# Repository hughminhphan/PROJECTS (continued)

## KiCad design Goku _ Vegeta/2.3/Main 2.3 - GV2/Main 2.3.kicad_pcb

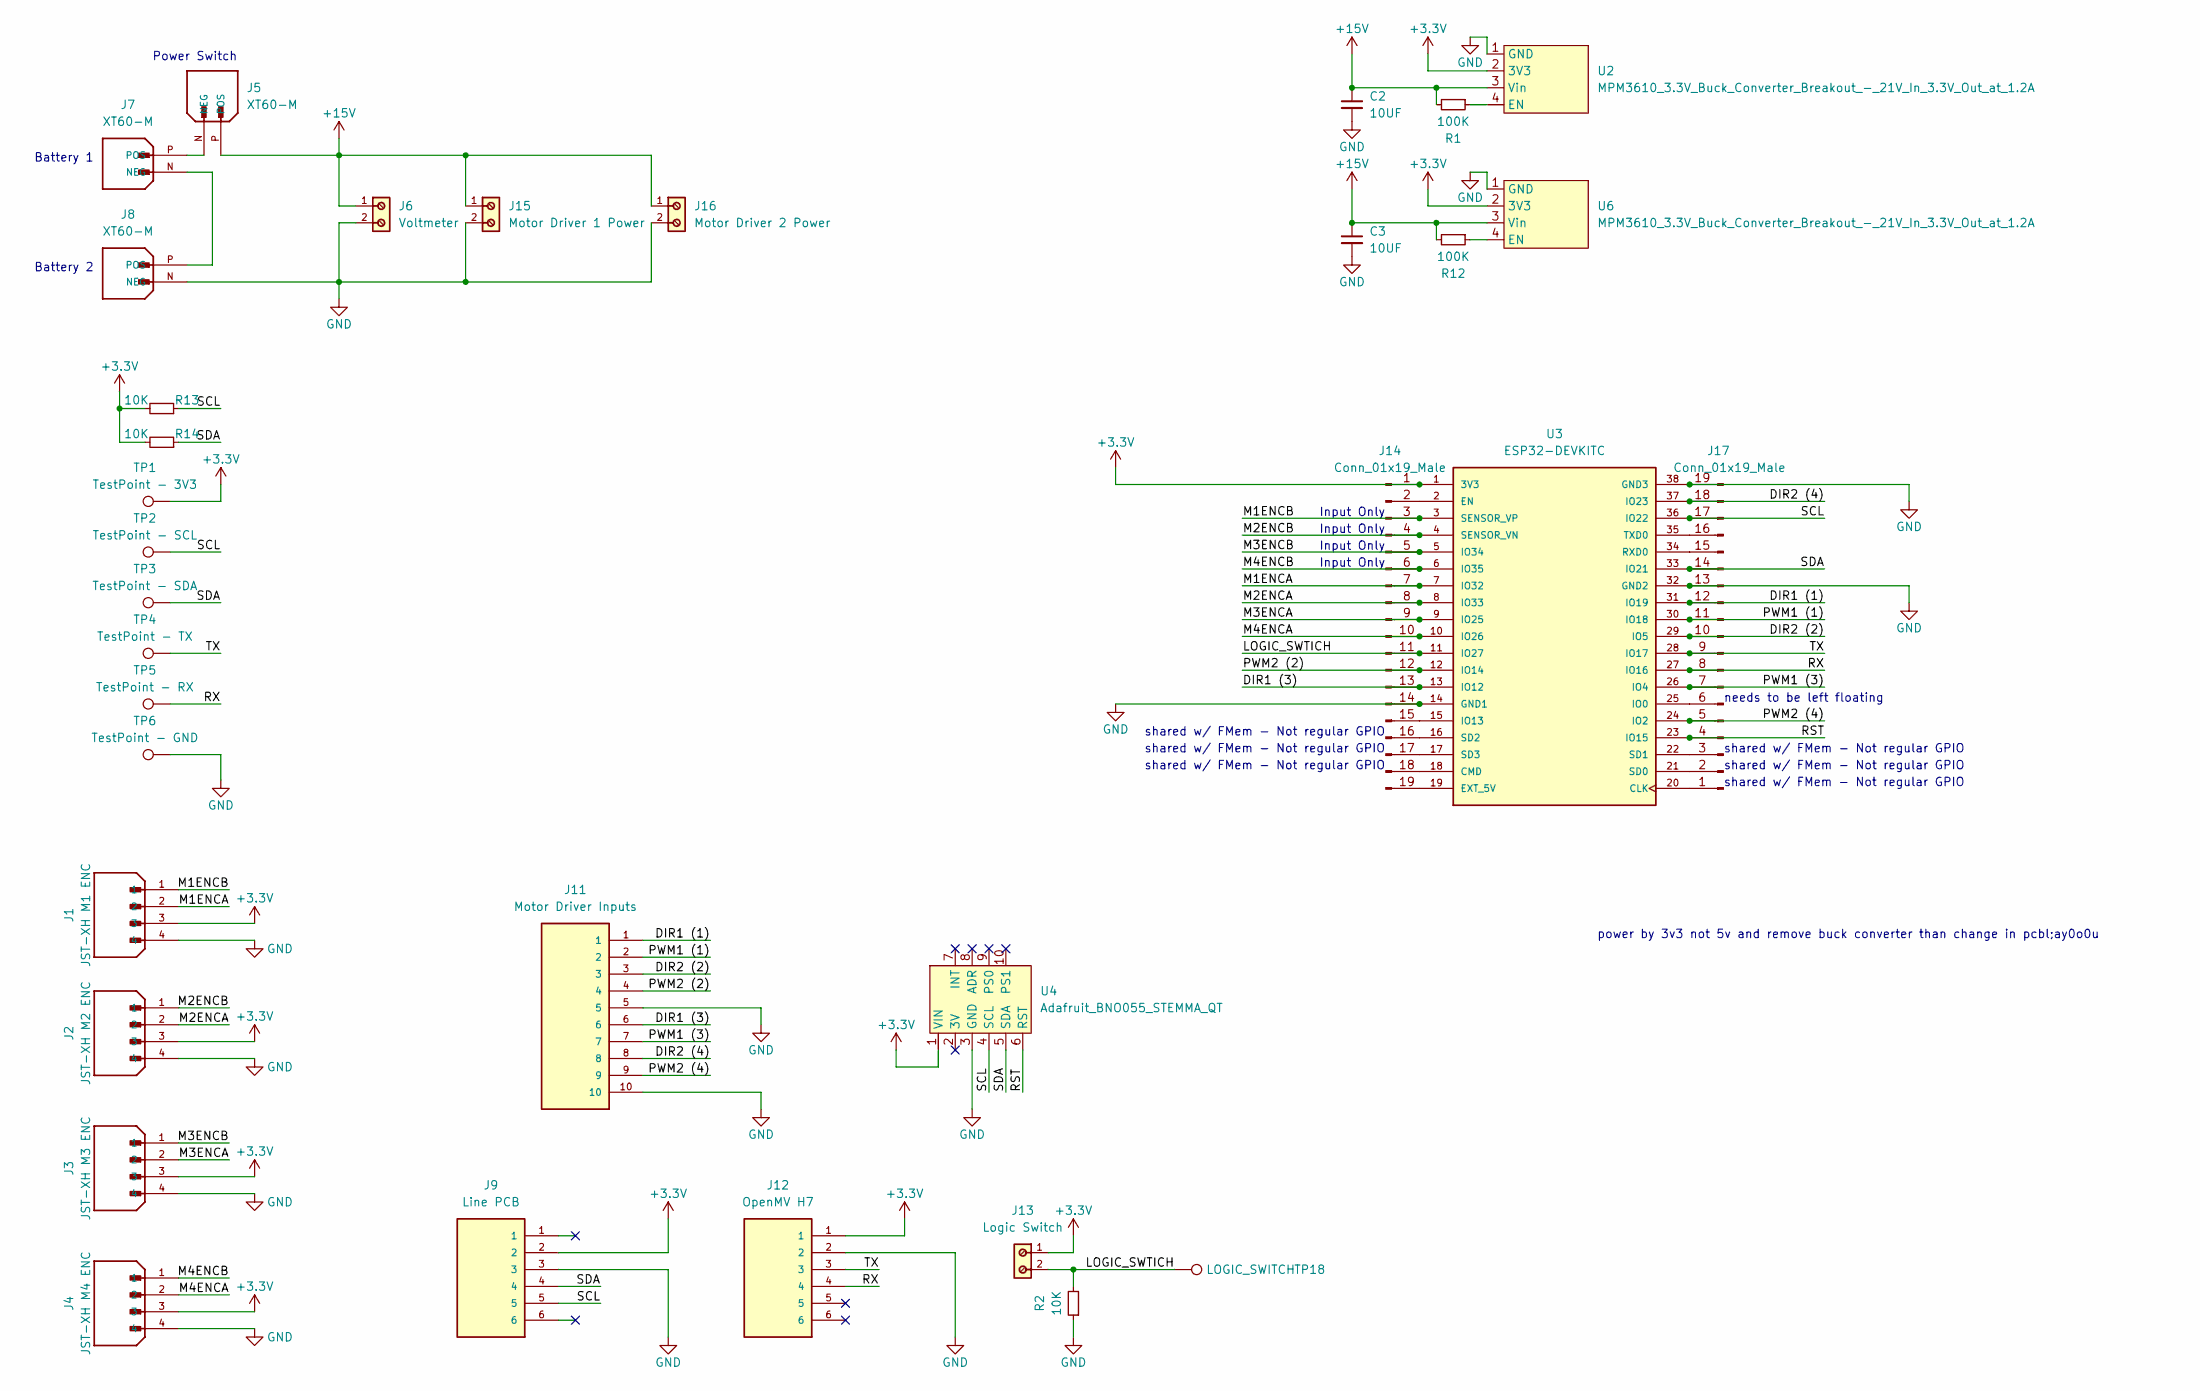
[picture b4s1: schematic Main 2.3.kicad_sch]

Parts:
C2, C3: 10UF; C_0805_2012Metric
J1: JST-XH M1 ENC; JST_B4B-XH-A(LF)(SN); PARTREV N/A
J2: JST-XH M2 ENC; JST_B4B-XH-A(LF)(SN); PARTREV N/A
J3: JST-XH M3 ENC; JST_B4B-XH-A(LF)(SN); PARTREV N/A
J4: JST-XH M4 ENC; JST_B4B-XH-A(LF)(SN); PARTREV N/A
J5, J7, J8: XT60-M; PARTREV V1.2
J6: Voltmeter; 5mm Pitch 2-Pin Screw Terminal Block; PART-NUMBER 691137710002
J9: Line PCB; Box IDC header 2x3
J11: Motor Driver Inputs; Box IDC header 2x5
J12: OpenMV H7; Box IDC header 2x3
J13: Logic Switch; 5mm Pitch 2-Pin Screw Terminal Block; PART-NUMBER 691137710002
J14, J17: Conn_01x19_Male; PinHeader_1x19_P2.54mm_Vertical
J15: Motor Driver 1 Power; 5mm Pitch 2-Pin Screw Terminal Block; PART-NUMBER 691137710002
J16: Motor Driver 2 Power; 5mm Pitch 2-Pin Screw Terminal Block; PART-NUMBER 691137710002
R1, R12: 100K; R_0805_2012Metric
R2, R13, R14: 10K; R_0805_2012Metric
TP1: TestPoint - 3V3; TestPoint_THTPad_D2.0mm_Drill1.0mm
TP2: TestPoint - SCL; TestPoint_THTPad_D2.0mm_Drill1.0mm
TP3: TestPoint - SDA; TestPoint_THTPad_D2.0mm_Drill1.0mm
TP4: TestPoint - TX; TestPoint_THTPad_D2.0mm_Drill1.0mm
TP5: TestPoint - RX; TestPoint_THTPad_D2.0mm_Drill1.0mm
TP6: TestPoint - GND; TestPoint_THTPad_D2.0mm_Drill1.0mm
TP18: LOGIC_SWITCH; TestPoint_THTPad_D2.0mm_Drill1.0mm
U2, U6: MPM3610_3.3V_Buck_Converter_Breakout_-_21V_In_3.3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; MPM3610 3.3V Buck Converter Breakout - 21V In 3.3V Out at 1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
U3: ESP32-DEVKITC; MODULE_ESP32-DEVKITC; PARTREV N/A
U4: Adafruit_BNO055_STEMMA_QT; Adafruit IMU BNO055

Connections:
+3.3V: J1.3, J2.3, J3.3, J4.3, J9.2, J12.1, J13.1, J14.1, R13.2, R14.2, TP1.1, U2.2 (3V3), U3.1 (3V3), U4.1 (VIN), U6.2 (3V3)
+15V: C2.1, C3.1, J5.P (POS), J6.1, J15.1, J16.1, R1.2, R12.2, U2.3 (Vin), U6.3 (Vin)
/DIR1 (1): J11.1, J17.12, U3.31 (IO19)
/DIR1 (3): J11.6, J14.13, U3.13 (IO12)
/DIR2 (2): J11.3, J17.10, U3.29 (IO5)
/DIR2 (4): J11.8, J17.18, U3.37 (IO23)
/LOGIC_SWTICH: J13.2, J14.11, R2.2, TP18.1, U3.11 (IO27)
/M1ENCA: J1.2, J14.7, U3.7 (IO32)
/M1ENCB: J1.1, J14.3, U3.3 (SENSOR_VP)
/M2ENCA: J2.2, J14.8, U3.8 (IO33)
/M2ENCB: J2.1, J14.4, U3.4 (SENSOR_VN)
/M3ENCA: J3.2, J14.9, U3.9 (IO25)
/M3ENCB: J3.1, J14.5, U3.5 (IO34)
/M4ENCA: J4.2, J14.10, U3.10 (IO26)
/M4ENCB: J4.1, J14.6, U3.6 (IO35)
/PWM1 (1): J11.2, J17.11, U3.30 (IO18)
/PWM1 (3): J11.7, J17.7, U3.26 (IO4)
/PWM2 (2): J11.4, J14.12, U3.12 (IO14)
/PWM2 (4): J11.9, J17.5, U3.24 (IO2)
/RST: J17.4, U3.23 (IO15), U4.6 (RST)
/RX: J12.4, J17.8, TP5.1, U3.27 (IO16)
/SCL: J9.5, J17.17, R13.1, TP2.1, U3.36 (IO22), U4.4 (SCL)
/SDA: J9.4, J17.14, R14.1, TP3.1, U3.33 (IO21), U4.5 (SDA)
/TX: J12.3, J17.9, TP4.1, U3.28 (IO17)
GND: C2.2, C3.2, J1.4, J2.4, J3.4, J4.4, J6.2, J8.N (NEG), J9.3, J11.5, J11.10, J12.2, J14.14, J15.2, J16.2, J17.13, J17.19, R2.1, TP6.1, U2.1 (GND), U3.14 (GND1), U3.32 (GND2), U3.38 (GND3), U4.3 (GND), U6.1 (GND)
unnamed: J5.N (NEG), J7.P (POS)
unnamed: J7.N (NEG), J8.P (POS)
unnamed: J14.2, U3.2 (EN)
unnamed: J14.15, U3.15 (IO13)
unnamed: J14.16, U3.16 (SD2)
unnamed: J14.17, U3.17 (SD3)
unnamed: J14.18, U3.18 (CMD)
unnamed: J14.19, U3.19 (EXT_5V)
unnamed: J17.1, U3.20 (CLK)
unnamed: J17.2, U3.21 (SD0)
unnamed: J17.3, U3.22 (SD1)
unnamed: J17.6, U3.25 (IO0)
unnamed: J17.15, U3.34 (RXD0)
unnamed: J17.16, U3.35 (TXD0)
unnamed: R1.1, U2.4 (EN)
unnamed: R12.1, U6.4 (EN)

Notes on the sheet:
Input Only
shared w/ FMem - Not regular GPIO
needs to be left floating
Battery 1
Power Switch
power by 3v3 not 5v and remove buck converter than change in pcbl;ay0o0u
Battery 2

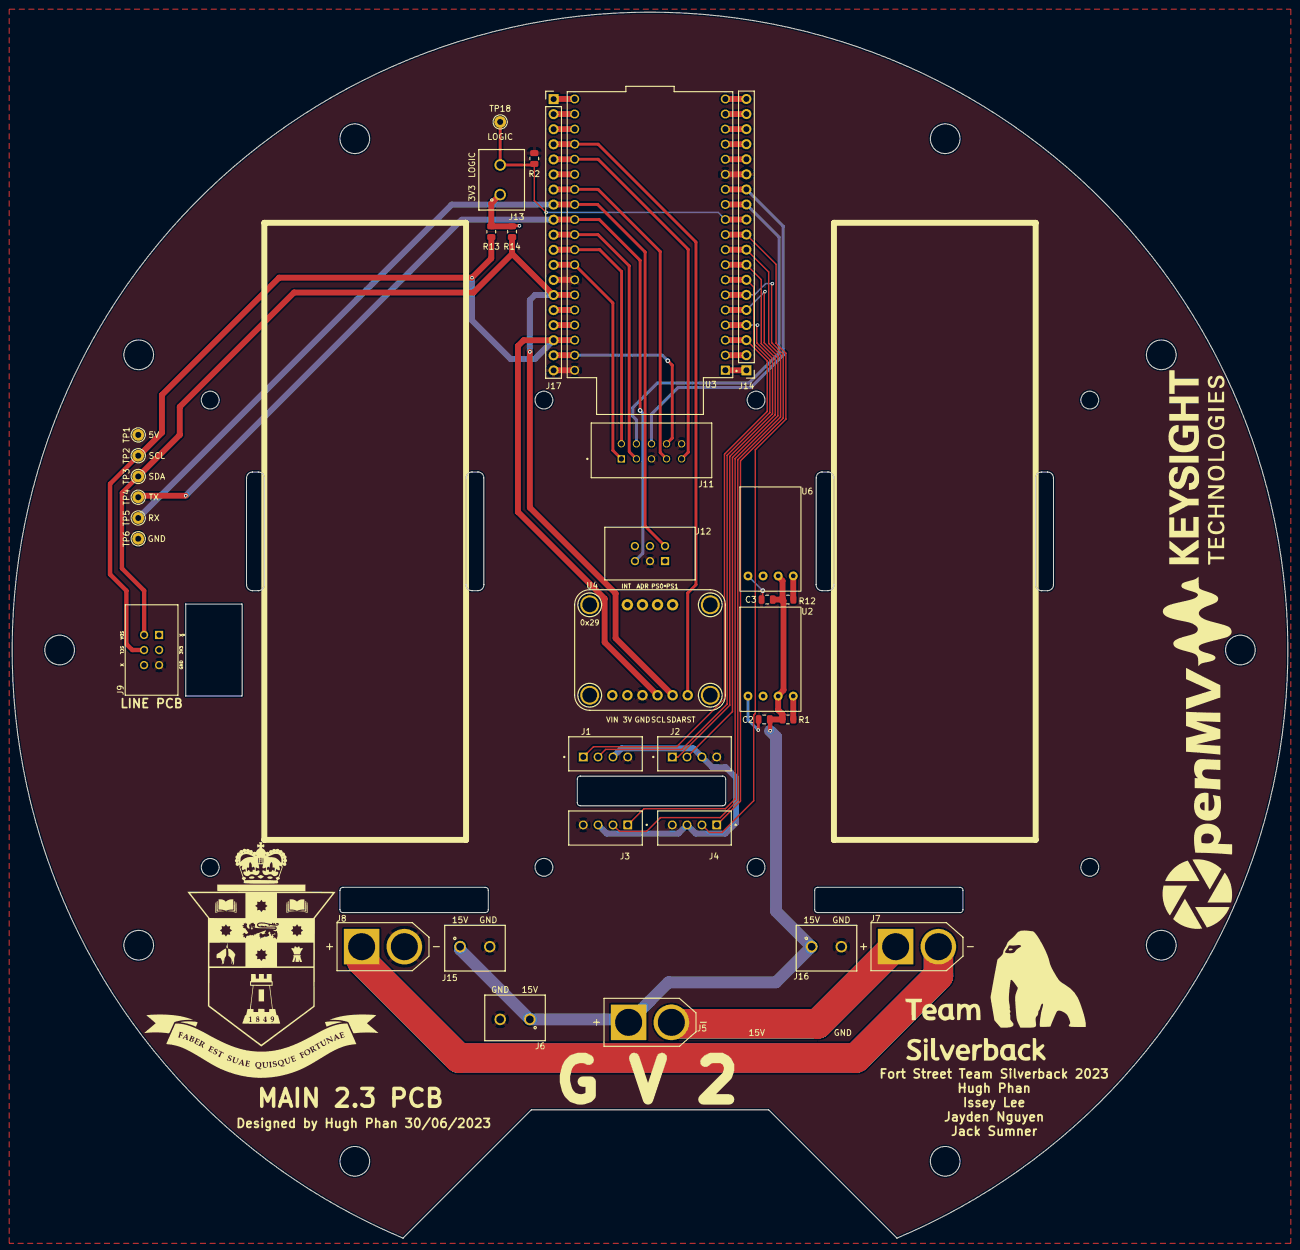
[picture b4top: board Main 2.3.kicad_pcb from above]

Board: 2 copper layers, 215.0 x 206.6 mm, 34 parts (0 on the bottom side), 41 nets.

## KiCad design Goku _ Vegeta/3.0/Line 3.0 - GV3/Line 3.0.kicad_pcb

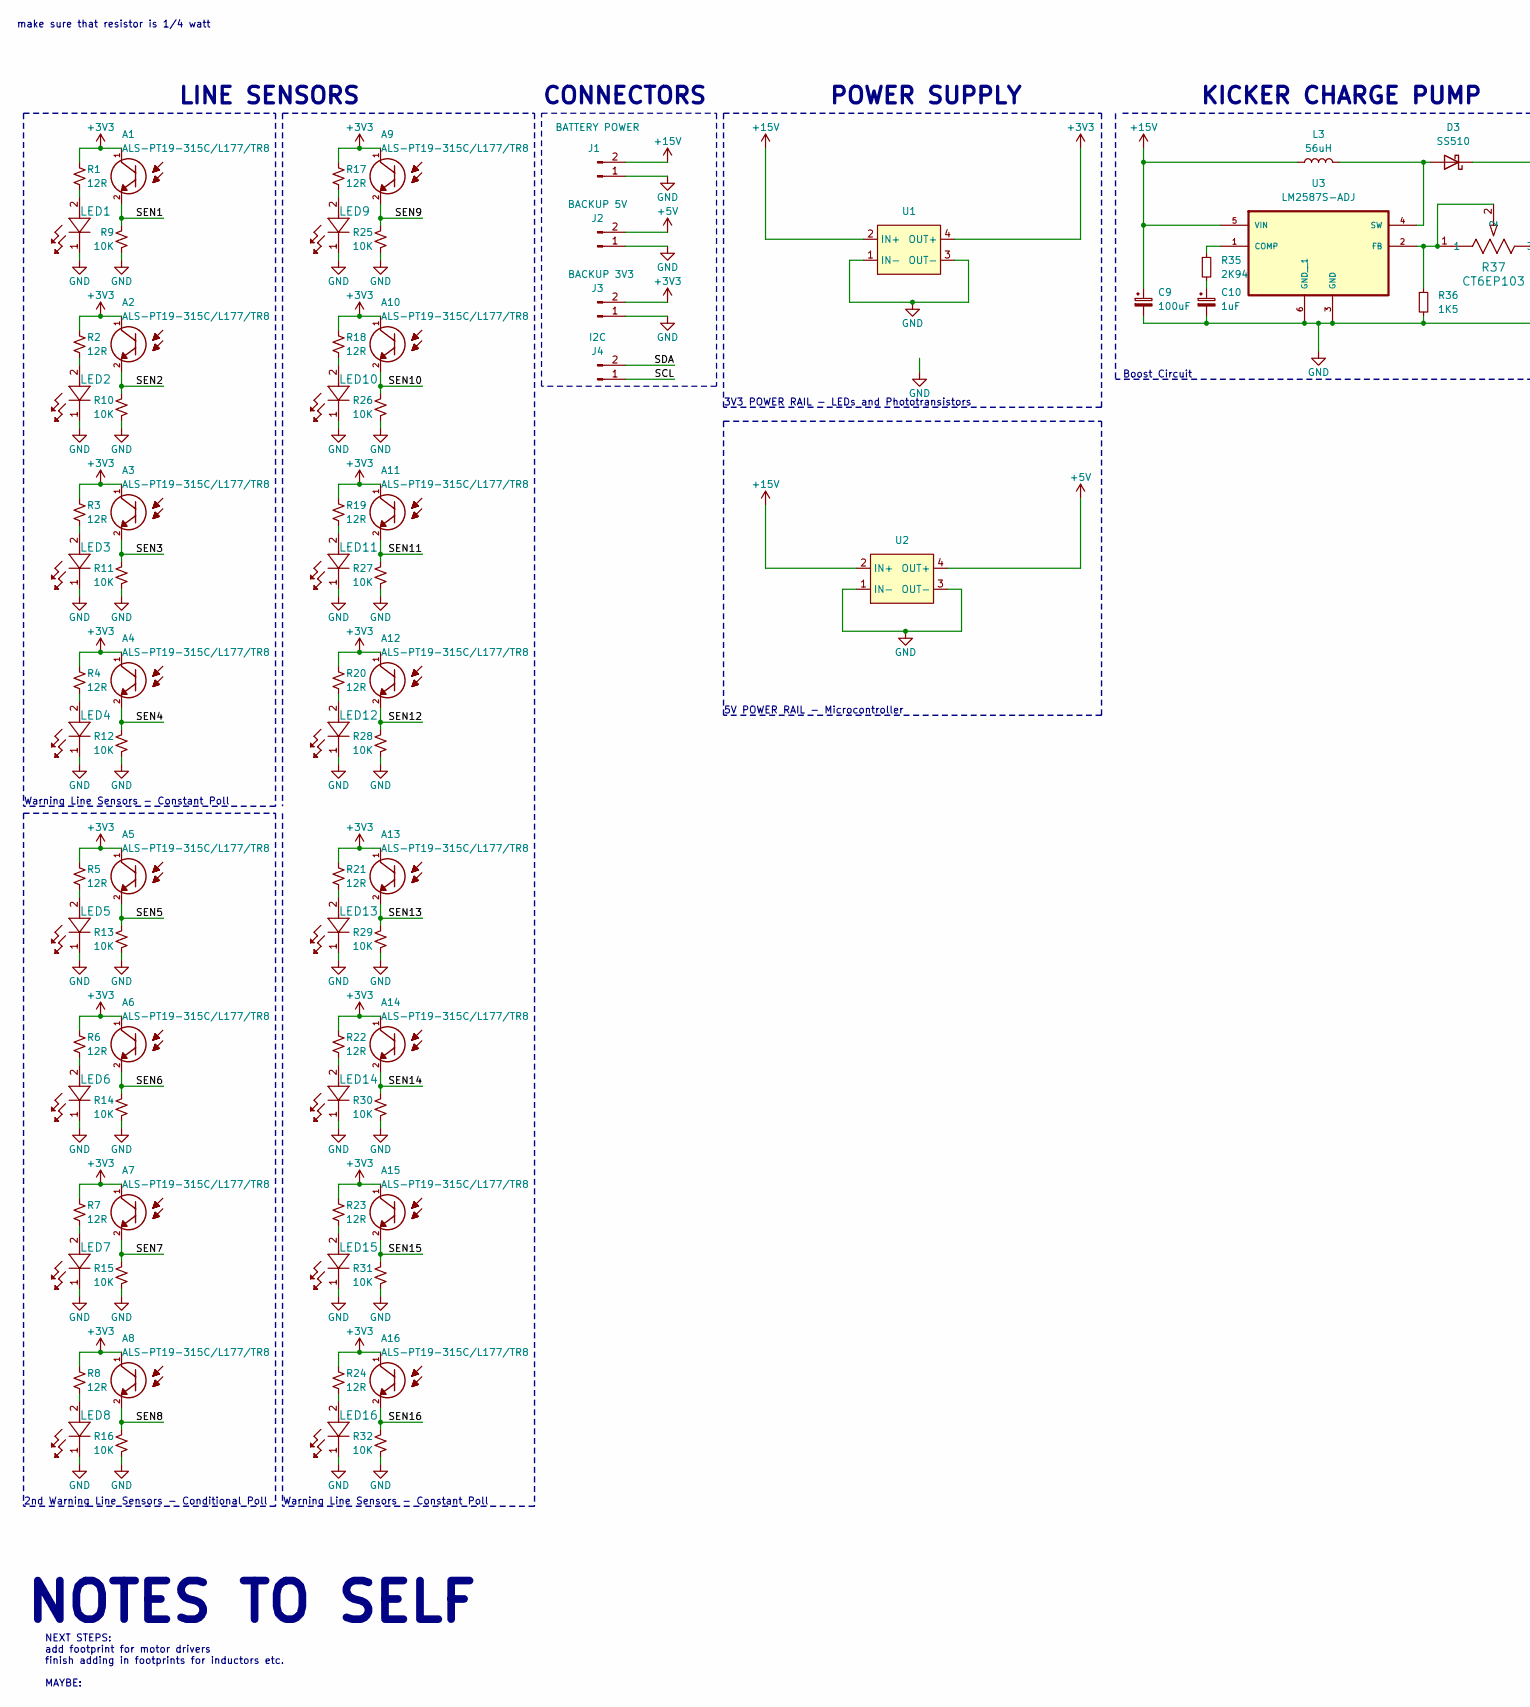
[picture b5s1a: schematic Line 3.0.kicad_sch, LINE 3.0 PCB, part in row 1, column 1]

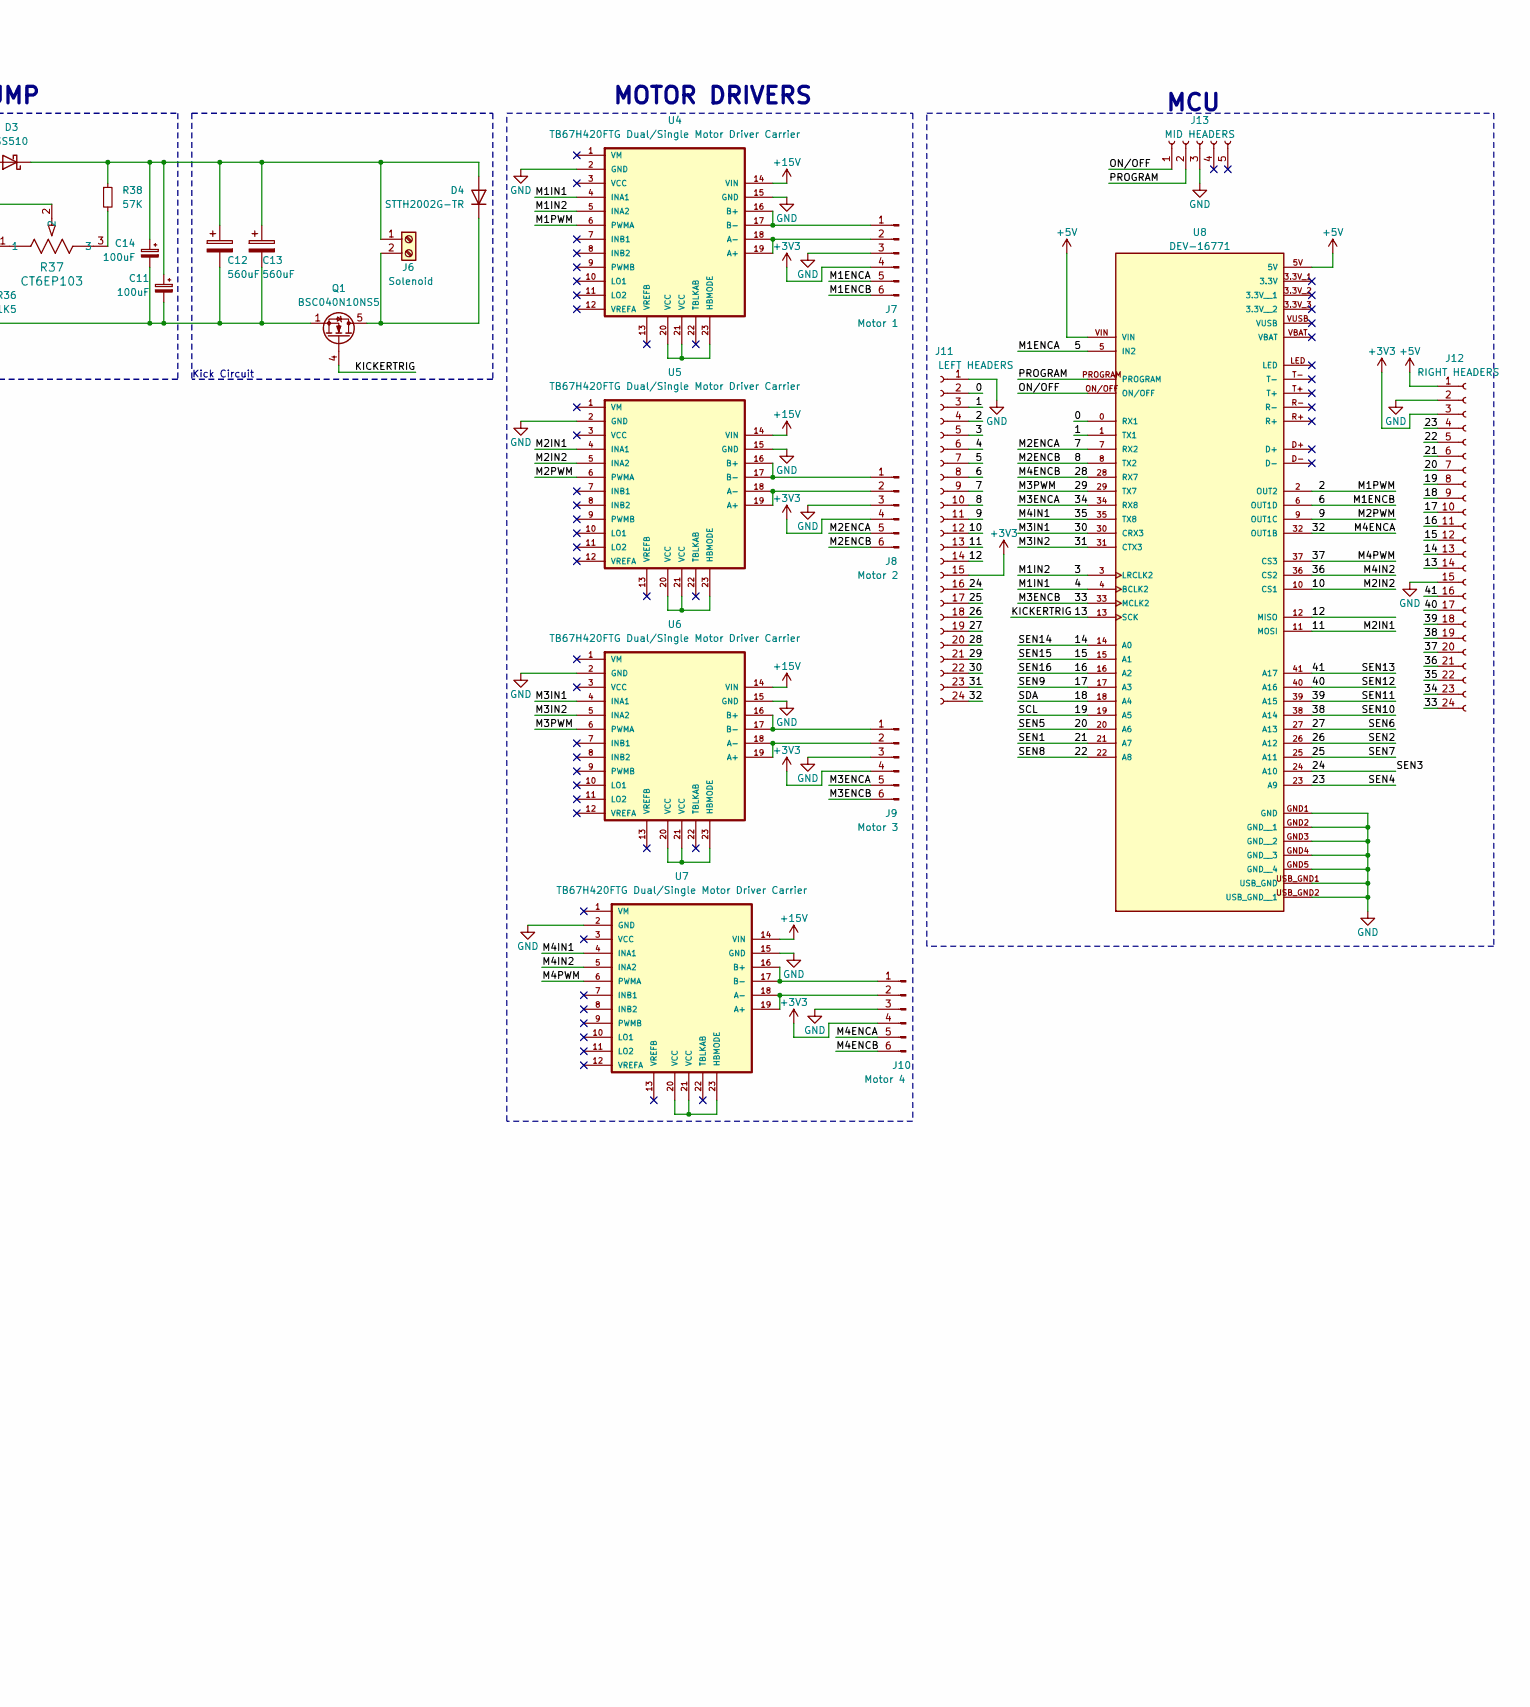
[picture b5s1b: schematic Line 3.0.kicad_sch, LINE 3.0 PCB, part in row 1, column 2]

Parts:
A1, A2, A3, A4, A5, A6, A7, A8, A9, A10, A11, A12, A13, A14, A15, A16: ALS-PT19-315C/L177/TR8; XDCR_ALS-PT19-315C_L177_TR8; PARTREV 5
C9, C11, C14: 100uF; CP_Radial_D10.0mm_P5.00mm
C10: 1uF; C_0805_2012Metric
C12, C13: 560uF; CP_Radial_D18.0mm_P7.50mm
D3: SS510; D_SMC
D4: STTH2002G-TR; TO-263-2
J1: BATTERY POWER; AMASS_XT60-F_1x02_P7.20mm_Vertical
J2: BACKUP 5V; AMASS_XT30U-F_1x02_P5.0mm_Vertical
J3: BACKUP 3V3; AMASS_XT30U-F_1x02_P5.0mm_Vertical
J4: I2C; AMASS_XT30U-F_1x02_P5.0mm_Vertical
J6: Solenoid; TerminalBlock_bornier-2_P5.08mm
J7: Motor 1; PinSocket_1x06_P2.54mm_Vertical
J8: Motor 2; PinSocket_1x06_P2.54mm_Vertical
J9: Motor 3; PinSocket_1x06_P2.54mm_Vertical
J10: Motor 4; PinSocket_1x06_P2.54mm_Vertical
J11: LEFT HEADERS; PinHeader_1x24_P2.54mm_Vertical
J12: RIGHT HEADERS; PinHeader_1x24_P2.54mm_Vertical
J13: MID HEADERS; PinHeader_1x05_P2.54mm_Vertical
L3: 56uH; L_Bourns_SRR1260
LED1, LED2, LED3, LED4, LED5, LED6, LED7, LED8, LED9, LED10, LED11, LED12, LED13, LED14, LED15, LED16: JB2835AWT-W-U30GA0000-N0000001; LED_J2835_CRW
Q1: BSC040N10NS5; TDSON-8-1
R1, R2, R3, R4, R5, R6, R7, R8, R17, R18, R19, R20, R21, R22, R23, R24: 12R; R_0805_2012Metric
R9, R10, R11, R12, R13, R14, R15, R16, R25, R26, R27, R28, R29, R30, R31, R32: 10K; R_0805_2012Metric
R35: 2K94; R_0805_2012Metric
R36: 1K5; R_0805_2012Metric
R37: CT6EP103; POT_CT-6EP_NDC
R38: 57K; R_0805_2012Metric
U1, U2: DC-DC Multi-output Buck Converter
U3: LM2587S-ADJ; VREG_TPS79625KTTR
U4, U5, U6, U7: TB67H420FTG Dual/Single Motor Driver Carrier; TB67H420FTG DualSingle Motor Driver Carrier
U8: DEV-16771; MODULE_DEV-16771; PARTREV 4.1

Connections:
+3V3: A1.1, A2.1, A3.1, A4.1, A5.1, A6.1, A7.1, A8.1, A9.1, A10.1, A11.1, A12.1, A13.1, A14.1, A15.1, A16.1, J3.2, J7.4, J8.4, J9.4, J10.4, J11.15, J12.3, R1.1, R2.1, R3.1, R4.1, R5.1, R6.1, R7.1, R8.1, R17.1, R18.1, R19.1, R20.1, R21.1, R22.1, R23.1, R24.1, U1.4 (OUT+); also elsewhere on the board
+5V: J2.2, J12.1, U2.4 (OUT+), U8.5V, U8.VIN; also elsewhere on the board
+15V: C9.1, J1.2, L3.1, U1.2 (IN+), U2.2 (IN+), U3.5 (VIN), U4.14 (VIN), U5.14 (VIN), U6.14 (VIN), U7.14 (VIN)
/0: J11.2, U8.0 (RX1)
/1: J11.3, U8.1 (TX1)
/2: J11.4, U4.6 (PWMA), U8.2 (OUT2)
/3: J11.5, U4.5 (INA2), U8.3 (LRCLK2)
/4: J11.6, U4.4 (INA1), U8.4 (BCLK2)
/5: J7.5, J11.7, U8.5 (IN2)
/6: J7.6, J11.8, U8.6 (OUT1D)
/7: J8.5, J11.9, U8.7 (RX2)
/8: J8.6, J11.10, U8.8 (TX2)
/9: J11.11, U5.6 (PWMA), U8.9 (OUT1C)
/10: J11.12, U5.5 (INA2), U8.10 (CS1)
/11: J11.13, U5.4 (INA1), U8.11 (MOSI)
/12: J11.14, U8.12 (MISO)
/13: J12.14, Q1.4 (G), U8.13 (SCK)
/14: A14.2, J12.13, R30.2, U8.14 (A0)
/15: A15.2, J12.12, R31.2, U8.15 (A1)
/16: A16.2, J12.11, R32.2, U8.16 (A2)
/17: A9.2, J12.10, R25.2, U8.17 (A3)
/18: J4.2, J12.9, U8.18 (A4)
/19: J4.1, J12.8, U8.19 (A5)
/20: A5.2, J12.7, R13.2, U8.20 (A6)
/21: A1.2, J12.6, R9.2, U8.21 (A7)
/22: A8.2, J12.5, R16.2, U8.22 (A8)
/23: A4.2, J12.4, R12.2, U8.23 (A9)
/24: A3.2, J11.16, R11.2, U8.24 (A10)
/25: A7.2, J11.17, R15.2, U8.25 (A11)
/26: A2.2, J11.18, R10.2, U8.26 (A12)
/27: A6.2, J11.19, R14.2, U8.27 (A13)
/28: J10.6, J11.20, U8.28 (RX7)
/29: J11.21, U6.6 (PWMA), U8.29 (TX7)
/30: J11.22, U6.4 (INA1), U8.30 (CRX3)
/31: J11.23, U6.5 (INA2), U8.31 (CTX3)
/32: J10.5, J11.24, U8.32 (OUT1B)
/33: J9.6, J12.24, U8.33 (MCLK2)
/34: J9.5, J12.23, U8.34 (RX8)
/35: J12.22, U7.4 (INA1), U8.35 (TX8)
/36: J12.21, U7.5 (INA2), U8.36 (CS2)
/37: J12.20, U7.6 (PWMA), U8.37 (CS3)
/38: A10.2, J12.19, R26.2, U8.38 (A14)
/39: A11.2, J12.18, R27.2, U8.39 (A15)
/40: A12.2, J12.17, R28.2, U8.40 (A16)
/41: A13.2, J12.16, R29.2, U8.41 (A17)
/ON/OFF: J13.1, U8.ON/OFF
/PROGRAM: J13.2, U8.PROGRAM
GND: C9.2, C10.2, C11.2, C12.2, C13.2, C14.2, J1.1, J2.1, J3.1, J7.3, J8.3, J9.3, J10.3, J11.1, J12.2, J12.15, J13.3, LED1.1, LED2.1, LED3.1, LED4.1, LED5.1, LED6.1, LED7.1, LED8.1, LED9.1, LED10.1, LED11.1, LED12.1, LED13.1, LED14.1, LED15.1, LED16.1, Q1.1 (S), Q1.2 (S), Q1.3 (S), R9.1, R10.1, R11.1, R12.1, R13.1, R14.1, R15.1, R16.1, R25.1, R26.1, R27.1, R28.1, R29.1, R30.1, R31.1, R32.1, R36.2, U1.1 (IN-), U1.3 (OUT-), U2.1 (IN-), U2.3 (OUT-), U3.3 (GND), U3.6 (GND__1), U4.2 (GND), U4.15 (GND), U5.2 (GND), U5.15 (GND), U6.2 (GND), U6.15 (GND), U7.2 (GND), U7.15 (GND), U8.GND1 (GND), U8.GND2 (GND__1), U8.GND3 (GND__2), U8.GND4 (GND__3), U8.GND5 (GND__4), U8.USB_GND1 (USB_GND), U8.USB_GND2 (USB_GND__1); also elsewhere on the board
unnamed: C10.1, R35.2
unnamed: D3.2 (A), L3.2, U3.4 (SW)
unnamed: C11.1, C12.1, C13.1, C14.1, D3.1 (K), D4.3 (A), J6.1, R38.1
unnamed: D4.2 (K), J6.2, Q1.5 (D)
unnamed: J7.1, U4.16 (B+), U4.17 (B-)
unnamed: J7.2, U4.18 (A-), U4.19 (A+)
unnamed: J8.1, U5.16 (B+), U5.17 (B-)
unnamed: J8.2, U5.18 (A-), U5.19 (A+)
unnamed: J9.1, U6.16 (B+), U6.17 (B-)
unnamed: J9.2, U6.18 (A-), U6.19 (A+)
unnamed: J10.1, U7.16 (B+), U7.17 (B-)
unnamed: J10.2, U7.18 (A-), U7.19 (A+)
unnamed: LED1.2, R1.2
unnamed: LED2.2, R2.2
unnamed: LED3.2, R3.2
unnamed: LED4.2, R4.2
unnamed: LED5.2, R5.2
unnamed: LED6.2, R6.2
unnamed: LED7.2, R7.2
unnamed: LED8.2, R8.2
unnamed: LED9.2, R17.2
unnamed: LED10.2, R18.2
unnamed: LED11.2, R19.2
unnamed: LED12.2, R20.2
unnamed: LED13.2, R21.2
unnamed: LED14.2, R22.2
unnamed: LED15.2, R23.2
unnamed: LED16.2, R24.2
unnamed: R37.3, R38.2
unnamed: R35.1, U3.1 (COMP)
unnamed: R36.1, R37.1, R37.2, U3.2 (FB)
unnamed: U4.20 (VCC), U4.21 (VCC), U4.23 (HBMODE)
unnamed: U5.20 (VCC), U5.21 (VCC), U5.23 (HBMODE)
unnamed: U6.20 (VCC), U6.21 (VCC), U6.23 (HBMODE)
unnamed: U7.20 (VCC), U7.21 (VCC), U7.23 (HBMODE)

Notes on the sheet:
NOTES TO SELF
NEXT STEPS: add footprint for motor drivers finish adding in footprints for inductors etc. MAYBE:
CONNECTORS
LINE SENSORS
2nd Warning Line Sensors - Conditional Poll
POWER SUPPLY
make sure that resistor is 1/4 watt
Warning Line Sensors - Constant Poll
Boost Circuit
Kick Circuit
5V POWER RAIL - Microcontroller
MCU
KICKER CHARGE PUMP
3V3 POWER RAIL - LEDs and Phototransistors
MOTOR DRIVERS

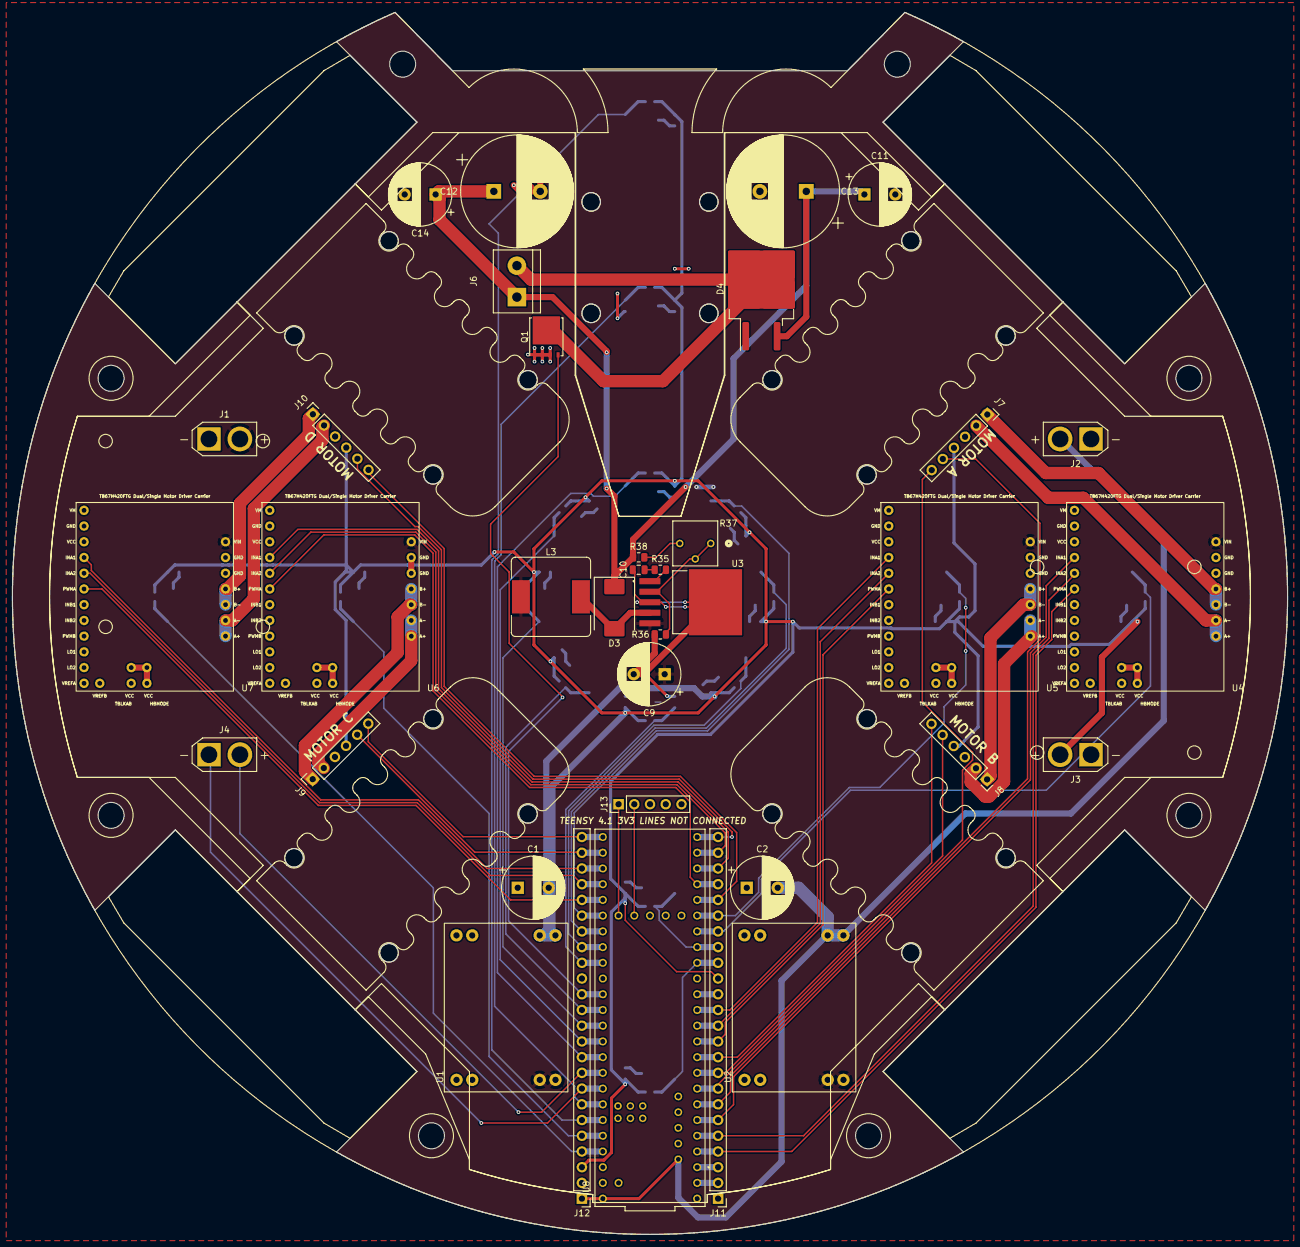
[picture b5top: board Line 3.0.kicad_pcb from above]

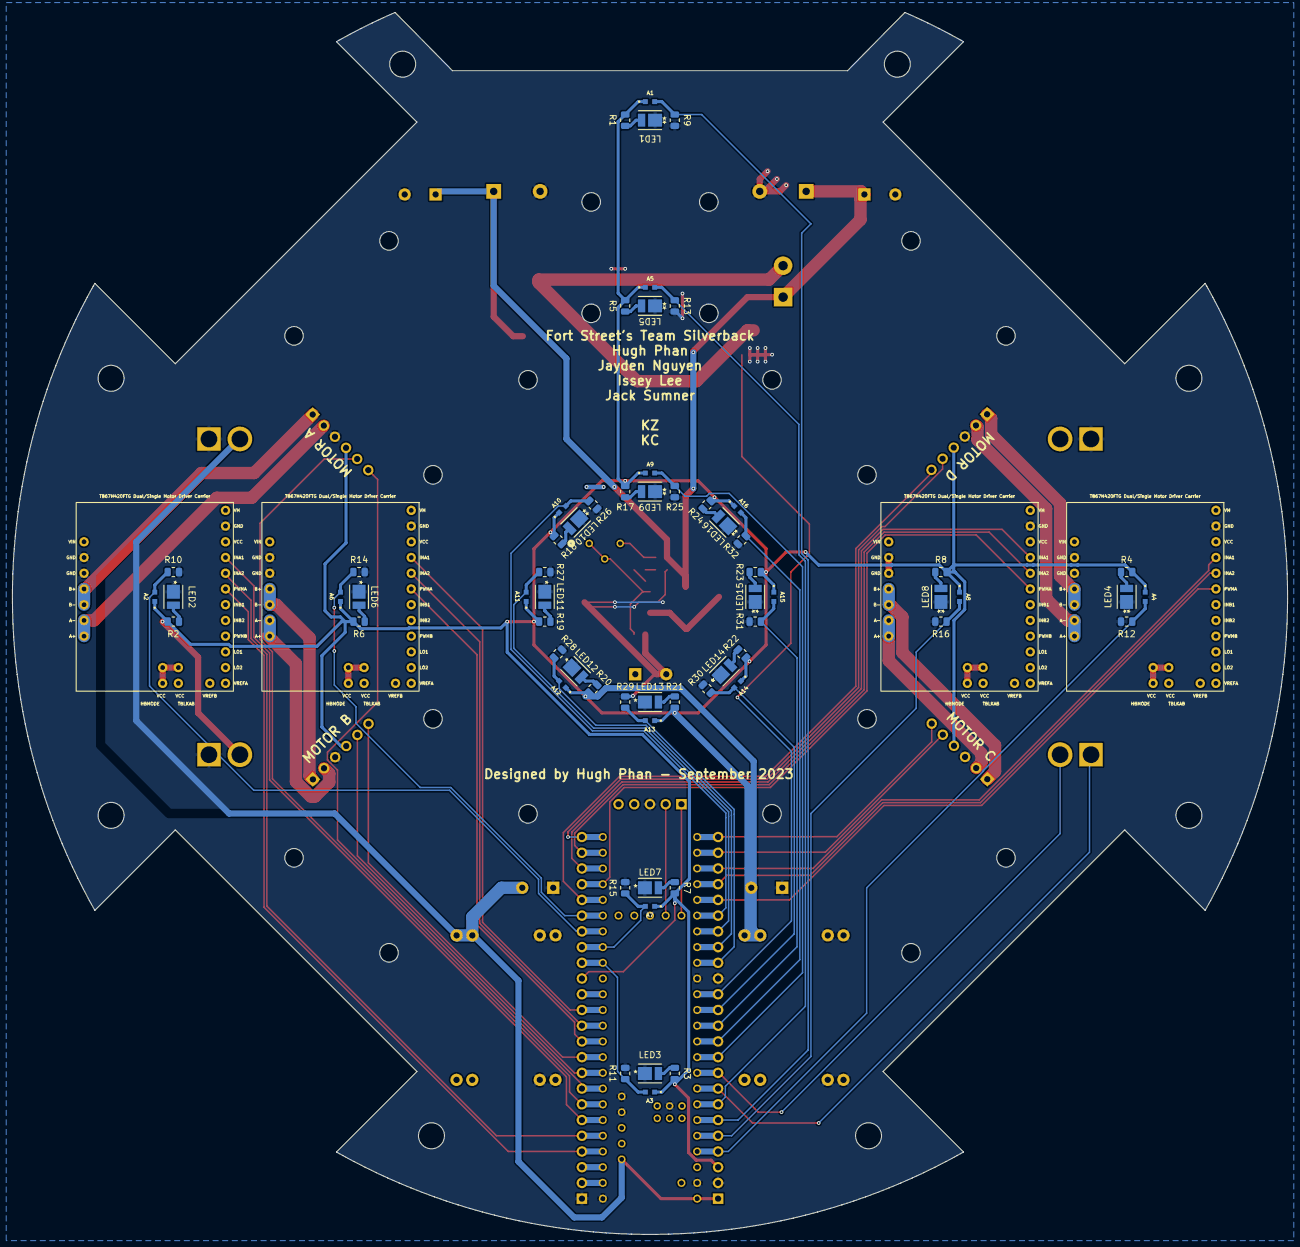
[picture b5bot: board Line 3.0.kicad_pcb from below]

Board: 2 copper layers, 206.0 x 197.4 mm, 100 parts (64 on the bottom side), 83 nets.

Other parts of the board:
C1, C2: 100uF; CP_Radial_D10.0mm_P5.00mm

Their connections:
+3V3: C1.2; also elsewhere on the board
+5V: C2.2; also elsewhere on the board
GND: C1.1, C2.1; also elsewhere on the board
